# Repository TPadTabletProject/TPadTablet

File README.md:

TPadTablet
==========

Projects developed for TPad Haptic Surface 
by Northwestern NxR Lab

<b>Applications:</b>
  * **IOIOAccessibilityService**: Haptic feedback as an android accessibility service
  * **HelloTPadTablet**: Demo app using on/off, time-based, and space based haptic textures
  * **TPadDepthMap**: Converts image into depth-based haptic feedback system
  * **TPadFrictionMap**: Uses pixels to create friction values for haptic surface
  * **TPadNexusLib**: Contains libraries used for other apps
  * **TimeTextureSampler**: App that allows you change amplitude and frequency of different wave forms for sampling haptic feedback.

Dev Notes:
	TexturePicApp should be fully merged with master branch at this point.

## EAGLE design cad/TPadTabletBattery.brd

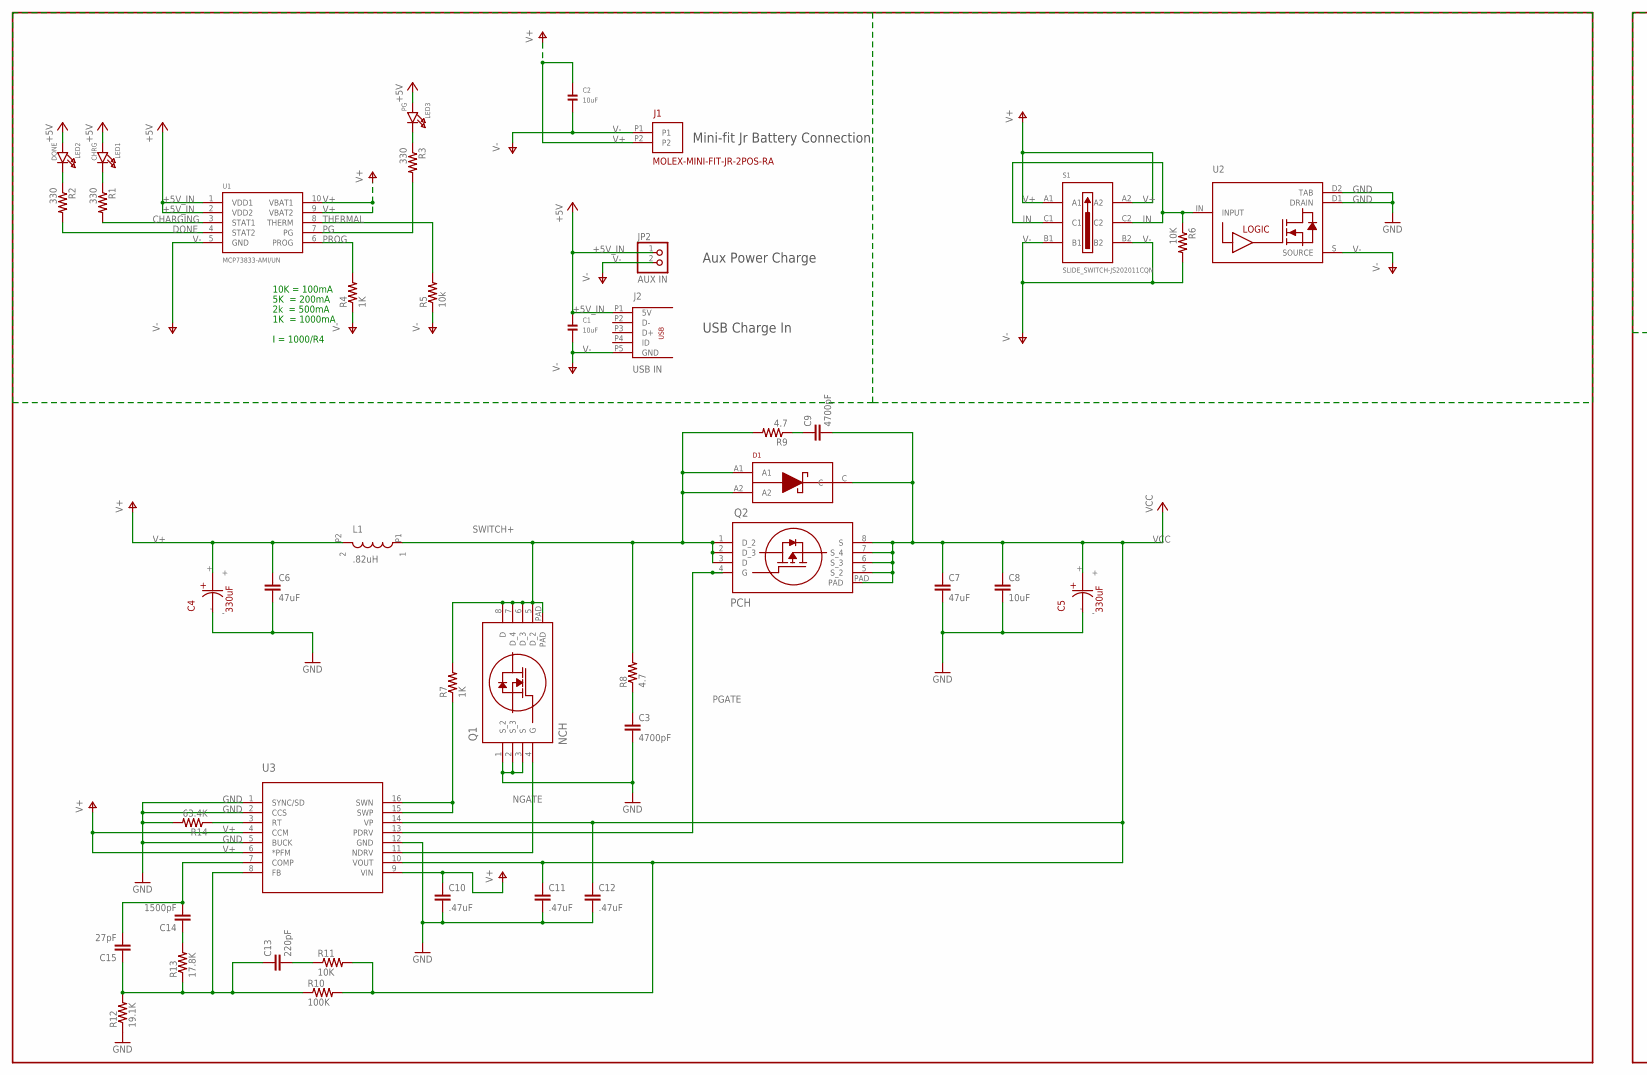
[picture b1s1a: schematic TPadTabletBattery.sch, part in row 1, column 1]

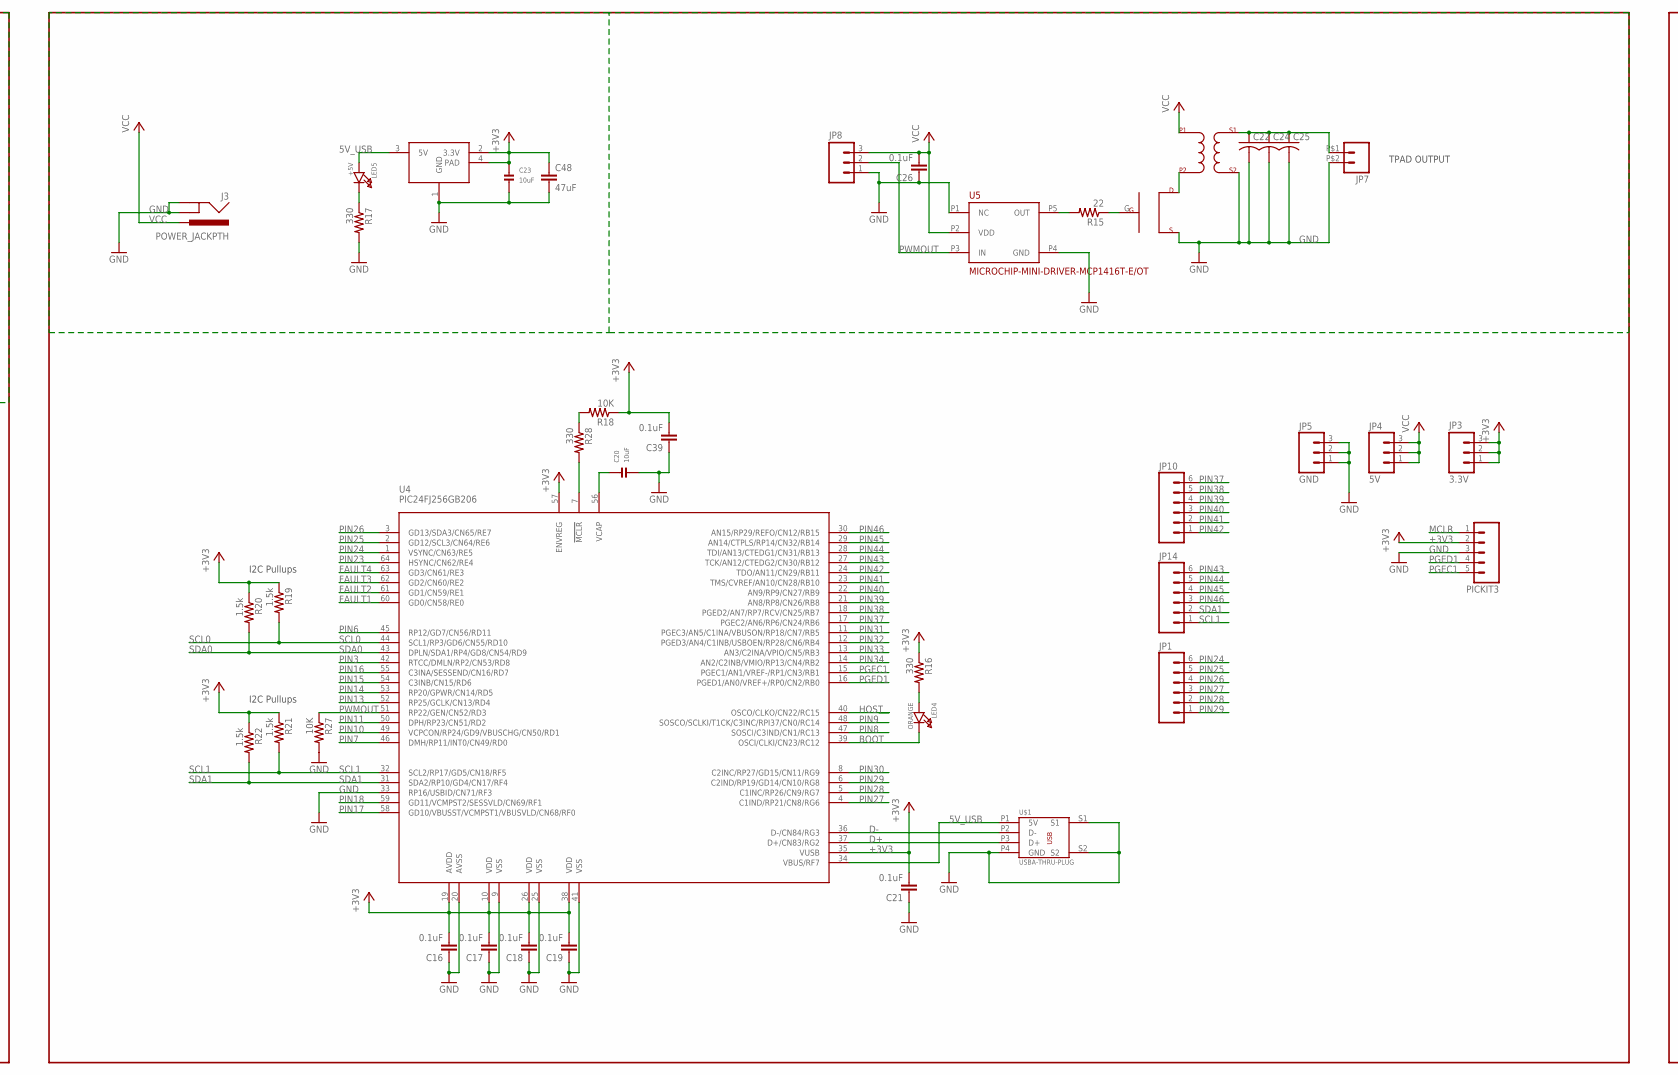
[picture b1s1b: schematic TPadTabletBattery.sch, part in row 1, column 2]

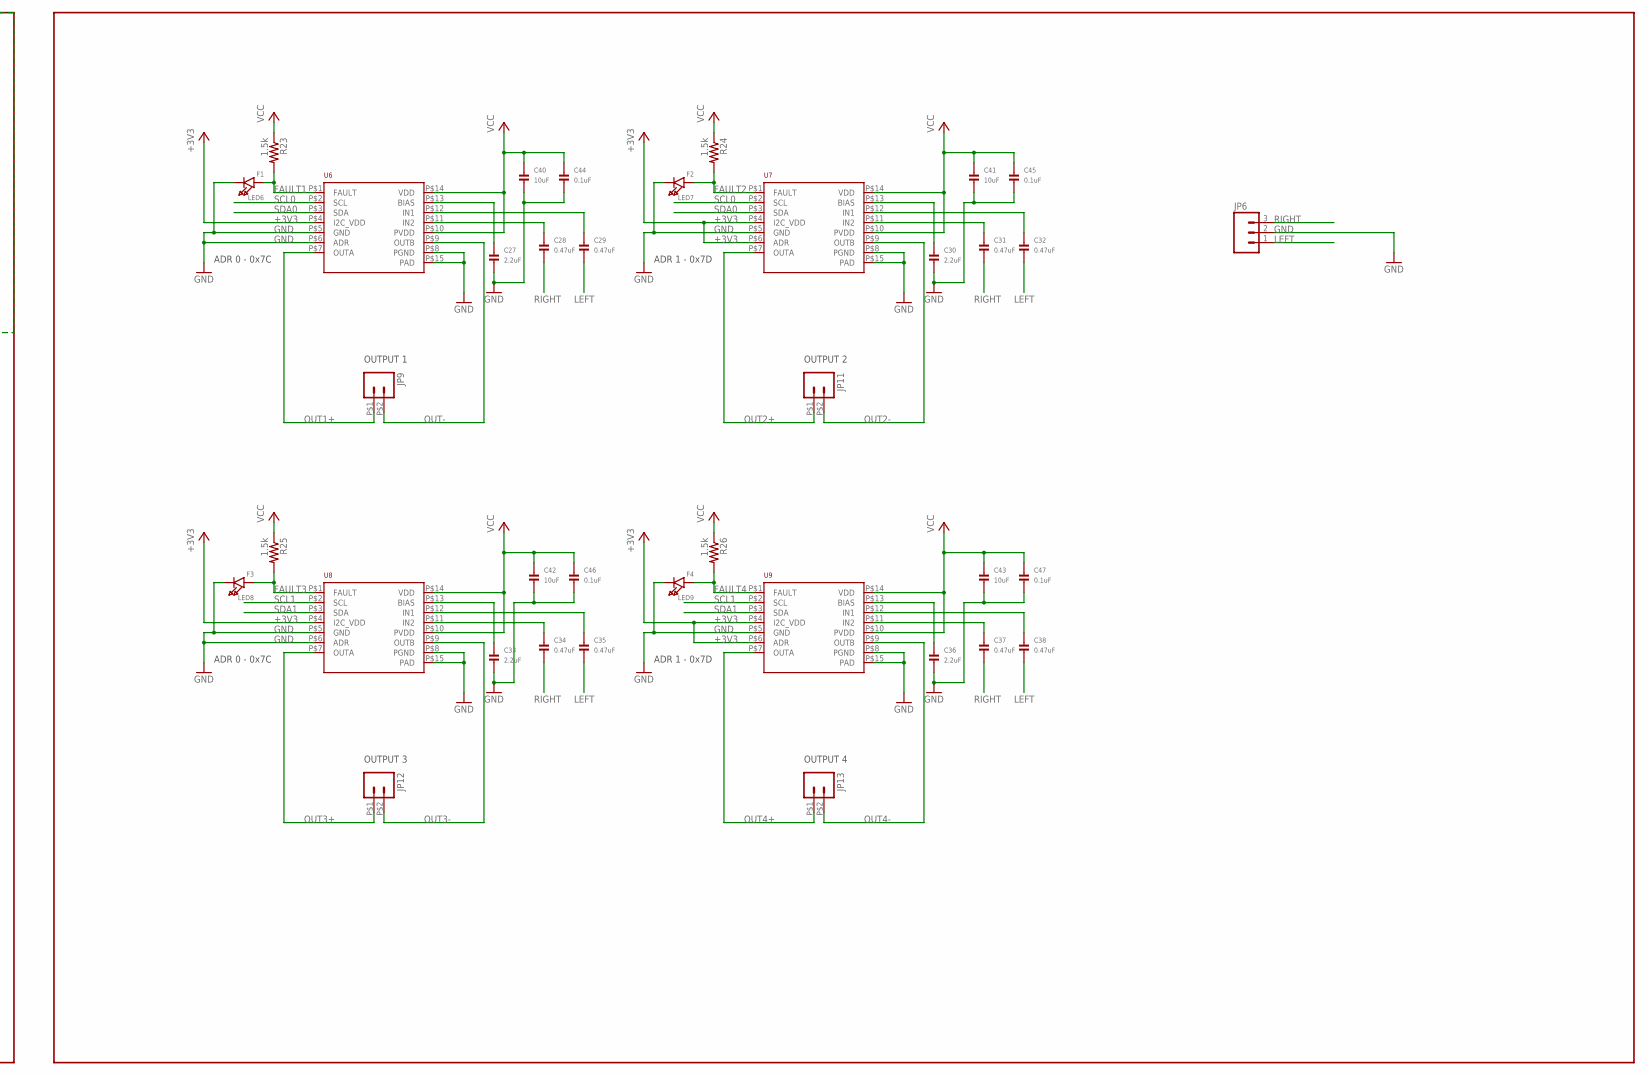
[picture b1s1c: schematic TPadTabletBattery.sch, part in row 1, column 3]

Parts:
C1, C2, C20, C23, C40, C41, C42, C43: 10uF; MICROBUILDER_0805
C3, C9: 4700pF; 0603-CAP
C4, C5: 330uF; 330UF_POSCAP
C6, C7, C48: 47uF; 1210
C8: 10uF; 0805
C10, C11, C12: .47uF; 0603-CAP
C13: 220pF; 0603-CAP
C14: 1500pF; 0603-CAP
C15: 27pF; 0603-CAP
C16, C17, C18, C19, C21, C26, C39: 0.1uF; 0603-CAP
C22, C24, C25: C-US050-035X075; C050-035X075
C27, C30, C33, C36: 2.2uF; MICROBUILDER_0603
C28, C29, C31, C32, C34, C35, C37, C38: 0.47uF; MICROBUILDER_0603
C44, C45, C46, C47: 0.1uF; MICROBUILDER_0603
D1: POWER-DIODE_PDS835L
J1: MOLEX-MINI-FIT-JR-2POS-RA
J2: USB IN; USBMICROBSMT
J3: POWER_JACKPTH; POWER_JACK_PTH
JP1, JP10, JP14: M06SIP; 1X06
JP2: AUX IN; MICROBUILDER_1X02_ROUND
JP3: 3.3V; 1X03
JP4: 5V; 1X03
JP5: GND; 1X03
JP6, JP8: M03PTH; 1X03
JP7, JP9, JP11, JP12, JP13: M02PTH2; 1X02_BIG
L1: .82uH; .82UH_INDUCTOR-IHLP3232DZERR82M01
LED1: CHRG; MICROBUILDER_CHIPLED_0603
LED2: DONE; MICROBUILDER_CHIPLED_0603
LED3: PG; MICROBUILDER_CHIPLED_0603
LED4: ORANGE; MICROBUILDER_CHIPLED_0603
LED5: +5V; MICROBUILDER_CHIPLED_0603
LED6: F1; MICROBUILDER_CHIPLED_0603
LED7: F2; MICROBUILDER_CHIPLED_0603
LED8: F3; MICROBUILDER_CHIPLED_0603
LED9: F4; MICROBUILDER_CHIPLED_0603
PICKIT3: M05PTH; 1X05
Q1: NCH; DQG8
Q2: PCH; DQG8
R1, R2, R3, R16, R17, R28: 330; 0603-RES
R4: 1K; 0805
R5: 10k; 0805
R6, R11, R18, R27: 10K; 0603-RES
R7: 1K; 0603-RES
R8, R9: 4.7; 0603-RES
R10: 100K; 0603-RES
R12: 19.1K; 0603-RES
R13: 17.8K; 0603-RES
R14: 63.4K; 0603-RES
R15: 22; 0603-RES
R19, R20, R21, R22, R23, R24, R25, R26: 1.5k; 0603-RES
S1: SLIDE_SWITCH-JS202011CQN
U1: MCP73833-AMI/UN; MICROBUILDER_MSOP10
U2: STM-LOW-SWITCH-VNL5050N3TR-E; SOT223
U3: TPS43000_PW_16; PW16
U4: PIC24FJ256GB206; PIC24FXXX_TQFP64
U5: MICROCHIP-MINI-DRIVER-MCP1416T-E/OT
U6, U7, U8, U9: TI-AUDIOAMP-LM48100Q
U$1: USBA-THRU-PLUG; USBA-THRU-FLUG
U$4: TRANSFORMER
U$5: TPAD_IRF520N; TPAD_TO220
U$6: LD33V; SOT223

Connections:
5V_USB: LED5.A, U4.34 (VBUS/RF7), U$1.P1 (5V), U$6.3 (5V)
+3V3: C16.2, C17.2, C18.2, C19.2, C21.2, C23.1, C39.2, C48.1, JP3.1, JP3.2, JP3.3, PICKIT3.2, R16.1, R18.1, R19.1, R20.1, R21.1, R22.1, U4.10 (VDD), U4.19 (AVDD), U4.26 (VDD), U4.35 (VUSB), U4.38 (VDD), U4.57 (ENVREG), U6.P$4 (I2C_VDD), U7.P$4 (I2C_VDD), U7.P$6 (ADR), U8.P$4 (I2C_VDD), U9.P$4 (I2C_VDD), U9.P$6 (ADR), U$6.2 (3.3V), U$6.4 (PAD)
+5V_IN: C1.1, J2.P1 (5V), JP2.1, LED1.A, LED2.A, LED3.A, U1.1 (VDD1), U1.2 (VDD2)
BOOT: LED4.C, U4.39 (OSCI/CLKI/CN23/RC12)
CHARGING: R1.2, U1.3 (STAT1)
D+: U4.37 (D+/CN83/RG2), U$1.P3 (D+)
D-: U4.36 (D-/CN84/RG3), U$1.P2 (D-)
DONE: R2.2, U1.4 (STAT2)
FAULT1: LED6.A, R23.2, U4.60 (GD0/CN58/RE0), U6.P$1 (FAULT)
FAULT2: LED7.A, R24.2, U4.61 (GD1/CN59/RE1), U7.P$1 (FAULT)
FAULT3: LED8.A, R25.2, U4.62 (GD2/CN60/RE2), U8.P$1 (FAULT)
FAULT4: LED9.A, R26.2, U4.63 (GD3/CN61/RE3), U9.P$1 (FAULT)
GND: C3.2, C4.-, C5.-, C6.2, C7.2, C8.2, C10.2, C11.2, C12.2, C16.1, C17.1, C18.1, C19.1, C20.2, C21.1, C22.2, C23.2, C24.2, C25.2, C26.1, C27.2, C30.2, C33.2, C36.2, C39.1, C40.2, C41.2, C42.2, C43.2, C44.2, C45.2, C46.2, C47.2, C48.2, J3.GND, J3.GNDBREAK, JP5.1, JP5.2, JP5.3, JP6.2, JP7.P$2 (2), JP8.1, LED6.C, LED7.C, LED8.C, LED9.C, PICKIT3.3, Q1.1 (S_2), Q1.2 (S_3), Q1.3 (S), R12.1, R14.2, R17.2, R27.2, U2.D1 (DRAIN), U2.D2 (TAB), U3.1 (SYNC/SD), U3.2 (CCS), U3.5 (BUCK), U3.12 (GND), U4.9 (VSS), U4.20 (AVSS), U4.25 (VSS), U4.33 (RP16/USBID/CN71/RF3), U4.41 (VSS), U5.P1 (NC), U5.P4 (GND), U6.P$5 (GND), U6.P$6 (ADR), U6.P$8 (PGND), U6.P$15 (PAD), U7.P$5 (GND), U7.P$8 (PGND), U7.P$15 (PAD), U8.P$5 (GND), U8.P$6 (ADR), U8.P$8 (PGND), U8.P$15 (PAD), U9.P$5 (GND), U9.P$8 (PGND), U9.P$15 (PAD), U$1.P4 (GND), U$1.S1, U$1.S2, U$4.S2, U$5.S, U$6.1 (GND)
HOST: U4.40 (OSCO/CLKO/CN22/RC15)
IN: R6.1, S1.C1, S1.C2, U2.IN (INPUT)
LEFT: C29.2, C32.2, C35.2, C38.2, JP6.1
MCLR: PICKIT3.1, R18.2, R28.1
unnamed: R7.1, U3.15 (SWP), U3.16 (SWN)
unnamed: LED2.C, R2.1
unnamed: LED1.C, R1.1
unnamed: LED3.C, R3.1
unnamed: R28.2, U4.7 (!MCLR)
unnamed: C9.1, R9.1
unnamed: C13.1, C15.1, R10.1, R12.2, R13.1, U3.8 (FB)
unnamed: C14.2, C15.2, U3.7 (COMP)
unnamed: C3.1, R8.1
unnamed: C20.1, U4.56 (VCAP)
unnamed: R14.1, U3.3 (RT)
unnamed: C14.1, R13.2
unnamed: LED4.A, R16.2
unnamed: C13.2, R11.1
unnamed: U$4.P2, U$5.D
unnamed: R15.2, U5.P5 (OUT)
unnamed: C22.1, C24.1, C25.1, JP7.P$1 (1), U$4.S1
unnamed: LED5.C, R17.1
unnamed: R15.1, U$5.G
unnamed: C27.1, U6.P$13 (BIAS)
unnamed: C29.1, U6.P$12 (IN1)
unnamed: C28.1, U6.P$11 (IN2)
unnamed: C30.1, U7.P$13 (BIAS)
unnamed: C32.1, U7.P$12 (IN1)
unnamed: C31.1, U7.P$11 (IN2)
unnamed: C33.1, U8.P$13 (BIAS)
unnamed: C35.1, U8.P$12 (IN1)
unnamed: C34.1, U8.P$11 (IN2)
unnamed: C36.1, U9.P$13 (BIAS)
unnamed: C38.1, U9.P$12 (IN1)
unnamed: C37.1, U9.P$11 (IN2)
NGATE: Q1.4 (G), U3.11 (NDRV)
OUT1+: JP9.P$1 (1), U6.P$7 (OUTA)
OUT2+: JP11.P$1 (1), U7.P$7 (OUTA)
OUT2-: JP11.P$2 (2), U7.P$9 (OUTB)
OUT3+: JP12.P$1 (1), U8.P$7 (OUTA)
OUT3-: JP12.P$2 (2), U8.P$9 (OUTB)
OUT4+: JP13.P$1 (1), U9.P$7 (OUTA)
OUT4-: JP13.P$2 (2), U9.P$9 (OUTB)
OUT-: JP9.P$2 (2), U6.P$9 (OUTB)
PG: R3.2, U1.7 (PG)
PGATE: Q2.4 (G), U3.13 (PDRV)
PGEC1: PICKIT3.5, U4.15 (PGEC1/AN1/VREF-/RP1/CN3/RB1)
PGED1: PICKIT3.4, U4.16 (PGED1/AN0/VREF+/RP0/CN2/RB0)
PIN3: U4.42 (RTCC/DMLN/RP2/CN53/RD8)
PIN6: U4.45 (RP12/GD7/CN56/RD11)
PIN7: U4.46 (DMH/RP11/INT0/CN49/RD0)
PIN8: U4.47 (SOSCI/C3IND/CN1/RC13)
PIN9: U4.48 (SOSCO/SCLKI/T1CK/C3INC/RPI37/CN0/RC14)
PIN10: U4.49 (VCPCON/RP24/GD9/VBUSCHG/CN50/RD1)
PIN11: U4.50 (DPH/RP23/CN51/RD2)
PIN13: U4.52 (RP25/GCLK/CN13/RD4)
PIN14: U4.53 (RP20/GPWR/CN14/RD5)
PIN15: U4.54 (C3INB/CN15/RD6)
PIN16: U4.55 (C3INA/SESSEND/CN16/RD7)
PIN17: U4.58 (GD10/VBUSST/VCMPST1/VBUSVLD/CN68/RF0)
PIN18: U4.59 (GD11/VCMPST2/SESSVLD/CN69/RF1)
PIN23: U4.64 (HSYNC/CN62/RE4)
PIN24: JP1.6, U4.1 (VSYNC/CN63/RE5)
PIN25: JP1.5, U4.2 (GD12/SCL3/CN64/RE6)
PIN26: JP1.4, U4.3 (GD13/SDA3/CN65/RE7)
PIN27: JP1.3, U4.4 (C1IND/RP21/CN8/RG6)
PIN28: JP1.2, U4.5 (C1INC/RP26/CN9/RG7)
PIN29: JP1.1, U4.6 (C2IND/RP19/GD14/CN10/RG8)
PIN30: U4.8 (C2INC/RP27/GD15/CN11/RG9)
PIN31: U4.11 (PGEC3/AN5/C1INA/VBUSON/RP18/CN7/RB5)
PIN32: U4.12 (PGED3/AN4/C1INB/USBOEN/RP28/CN6/RB4)
PIN33: U4.13 (AN3/C2INA/VPIO/CN5/RB3)
PIN34: U4.14 (AN2/C2INB/VMIO/RP13/CN4/RB2)
PIN37: JP10.6, U4.17 (PGEC2/AN6/RP6/CN24/RB6)
PIN38: JP10.5, U4.18 (PGED2/AN7/RP7/RCV/CN25/RB7)
PIN39: JP10.4, U4.21 (AN8/RP8/CN26/RB8)
PIN40: JP10.3, U4.22 (AN9/RP9/CN27/RB9)
PIN41: JP10.2, U4.23 (TMS/CVREF/AN10/CN28/RB10)
PIN42: JP10.1, U4.24 (TDO/AN11/CN29/RB11)
PIN43: JP14.6, U4.27 (TCK/AN12/CTEDG2/CN30/RB12)
PIN44: JP14.5, U4.28 (TDI/AN13/CTEDG1/CN31/RB13)
PIN45: JP14.4, U4.29 (AN14/CTPLS/RP14/CN32/RB14)
PIN46: JP14.3, U4.30 (AN15/RP29/REFO/CN12/RB15)
PROG: R4.2, U1.6 (PROG)
PWMOUT: JP8.2, R27.1, U4.51 (RP22/GEN/CN52/RD3), U5.P3 (IN)
RIGHT: C28.2, C31.2, C34.2, C37.2, JP6.3
SCL0: R19.2, U4.44 (SCL1/RP3/GD6/CN55/RD10), U6.P$2 (SCL), U7.P$2 (SCL)
SCL1: JP14.1, R21.2, U4.32 (SCL2/RP17/GD5/CN18/RF5), U8.P$2 (SCL), U9.P$2 (SCL)
SDA0: R20.2, U4.43 (DPLN/SDA1/RP4/GD8/CN54/RD9), U6.P$3 (SDA), U7.P$3 (SDA)
SDA1: JP14.2, R22.2, U4.31 (SDA2/RP10/GD4/CN17/RF4), U8.P$3 (SDA), U9.P$3 (SDA)
SWITCH+: D1.A1, D1.A2, L1.P1 (1), Q1.5 (D_2), Q1.6 (D_3), Q1.7 (D_4), Q1.8 (D), Q1.PAD, Q2.1 (D_2), Q2.2 (D_3), Q2.3 (D), R7.2, R8.2, R9.2
THERMAL: R5.2, U1.8 (THERM)
V+: C2.1, C4.+, C6.1, C10.1, J1.P2, L1.P2 (2), S1.A1, S1.A2, U1.9 (VBAT2), U1.10 (VBAT1), U3.4 (CCM), U3.6 (*PFM), U3.9 (VIN)
V-: C1.2, C2.2, J1.P1, J2.P5 (GND), JP2.2, R4.1, R5.1, R6.2, S1.B1, S1.B2, U1.5 (GND), U2.S (SOURCE)
VCC: C5.+, C7.1, C8.1, C9.2, C11.1, C12.1, C26.2, C40.1, C41.1, C42.1, C43.1, C44.1, C45.1, C46.1, C47.1, D1.C, J3.PWR, JP4.1, JP4.2, JP4.3, JP8.3, Q2.5 (S_2), Q2.6 (S_3), Q2.7 (S_4), Q2.8 (S), Q2.PAD, R10.2, R11.2, R23.1, R24.1, R25.1, R26.1, U3.10 (VOUT), U3.14 (VP), U5.P2 (VDD), U6.P$10 (PVDD), U6.P$14 (VDD), U7.P$10 (PVDD), U7.P$14 (VDD), U8.P$10 (PVDD), U8.P$14 (VDD), U9.P$10 (PVDD), U9.P$14 (VDD), U$4.P1

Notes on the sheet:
10K = 100mA
5K = 200mA
2k = 500mA
1K = 1000mA
I = 1000/R4
Mini-fit Jr Battery Connection
USB Charge In
Aux Power Charge
ADR 0 - 0x7C
I2C Pullups
OUTPUT 1
TPAD OUTPUT
OUTPUT 2
ADR 1 - 0x7D
OUTPUT 3
OUTPUT 4

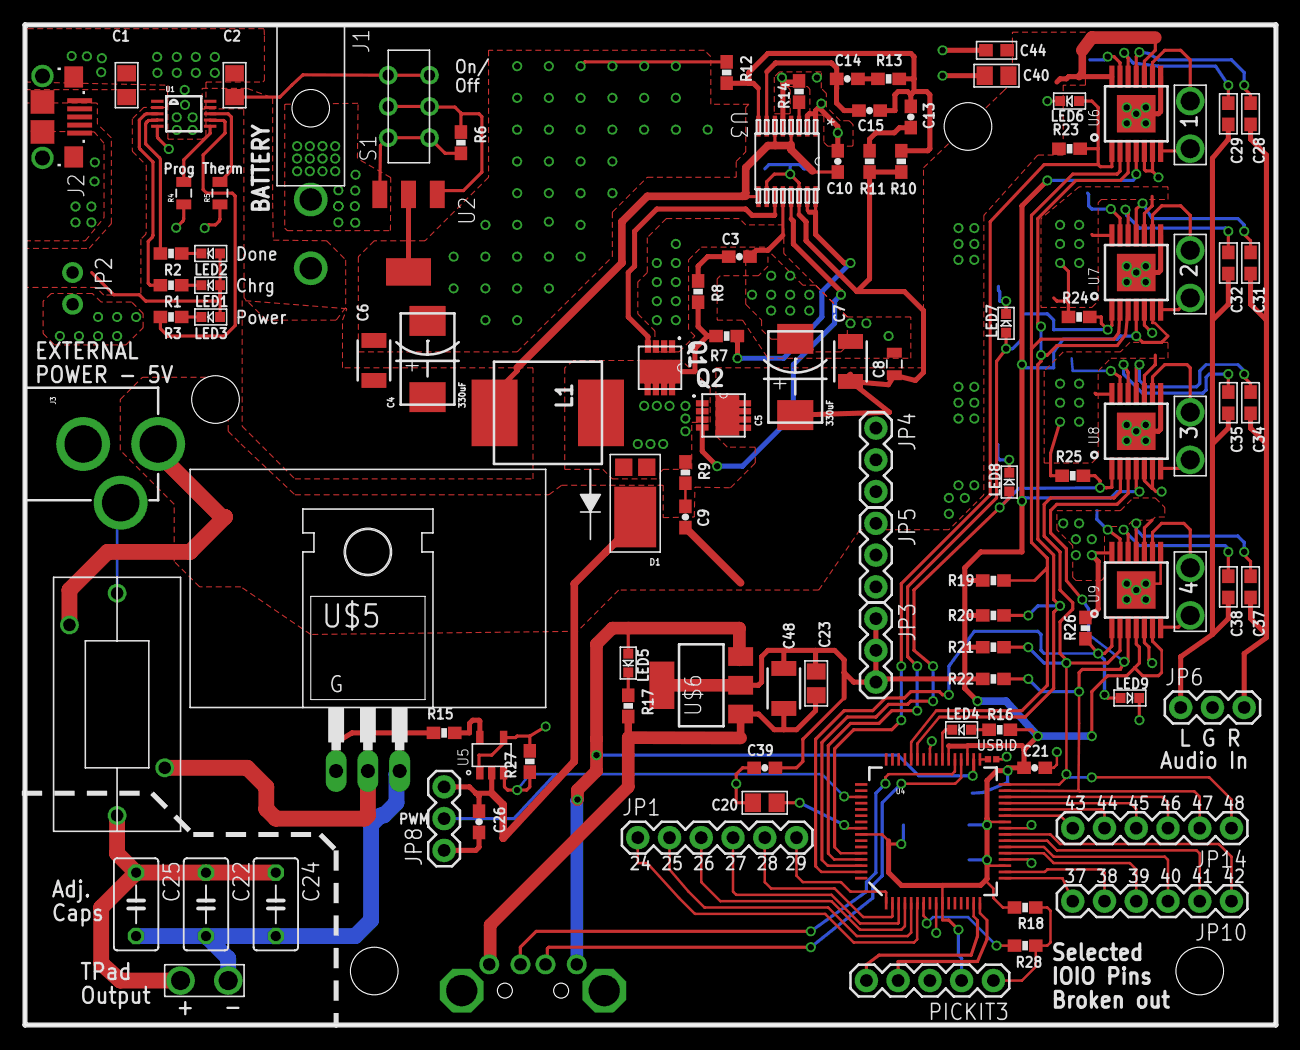
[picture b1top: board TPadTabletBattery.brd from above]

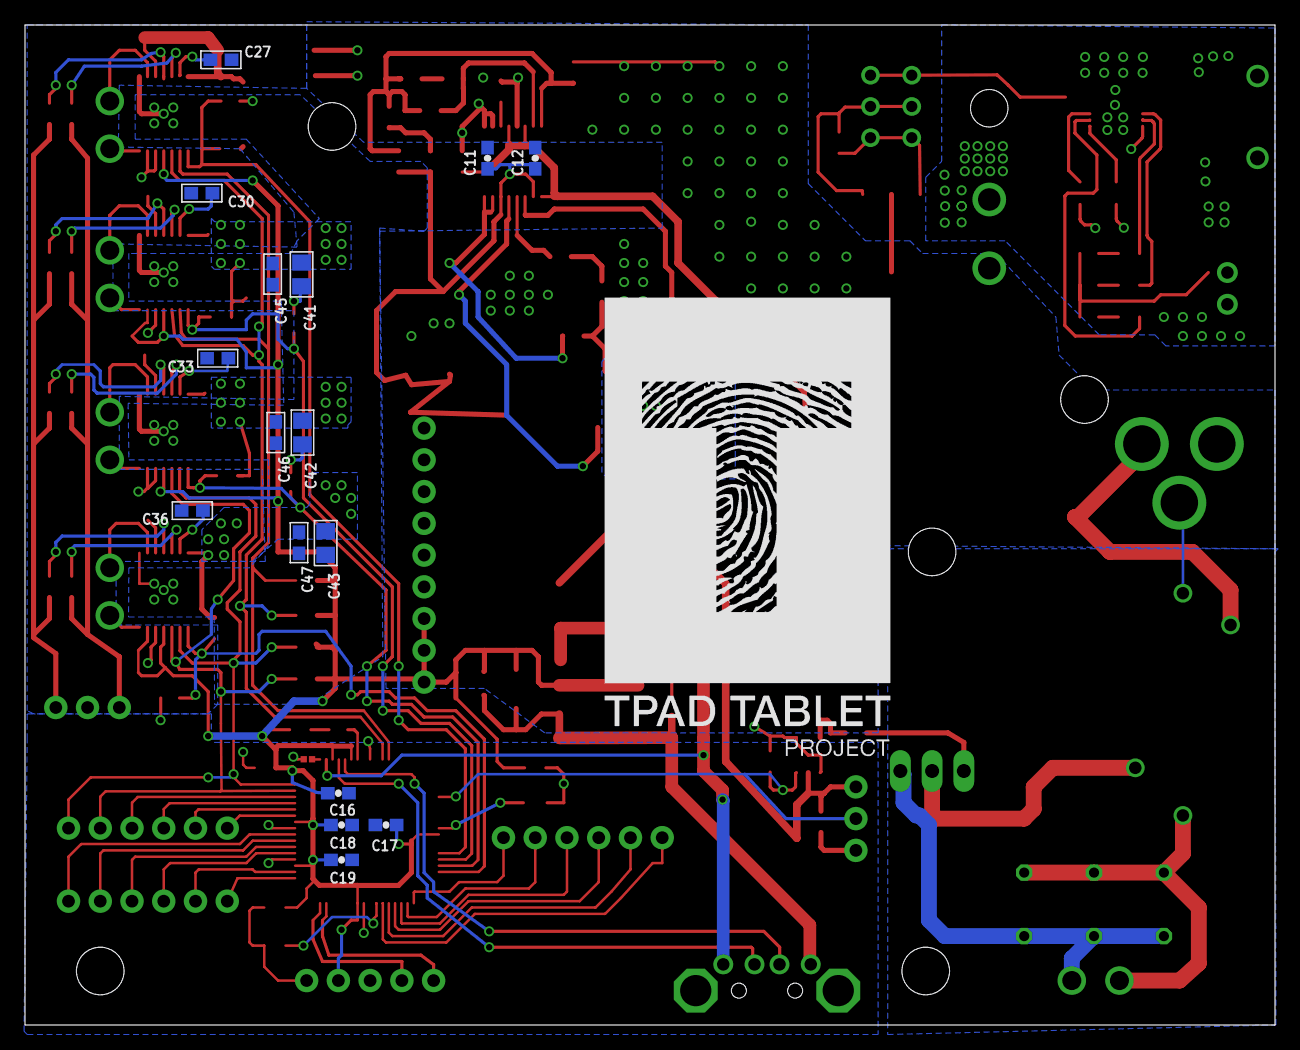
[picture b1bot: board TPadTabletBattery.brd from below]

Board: 2 copper layers, 100.0 x 80.0 mm, 122 parts (17 on the bottom side), 88 nets.

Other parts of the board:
U$2: TPADTABLETPROJECT

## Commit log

2014-06-16 Initial Library Commit
    This includes the TPadIOIO library to be used with the Nexus 7 TPads.
    Also included is a HelloWorld TPad Example application
2014-06-16 Fixing TPadIOIOLib support jar issue
2014-06-16 Update June 16th
2014-06-16 Uploading Demo Apps
    Upload Workshop and Gradient Demos
2014-06-17 Renaming Apps and Libraires
2014-06-18 Changes to HelloTPadTablet
    Also include some changes and additions to TPadNexusLib
2014-06-20 updating readme
2014-06-20 added incomplete project listing
2014-06-20 quick fix
2014-06-23 Including pre-compiled IOIO .jar files
    The TPadNexus Library now has the IOIO libraries included with it in the
    libs folder
2014-06-25 Fixed OpenCV Loading error
    The app will now ask for you to install the opencv manager if it is
    not
    already installed on the tablet.
2014-06-25 Changed Paths to Relative
    Changed TPadNexusLibrary to include relative path .jar files
2014-06-30 Added support for binding to background service to get Frequency
2014-07-01 ioio accessibility service
2014-07-01 Updates to HelloTPadTablet
2014-07-01 Revert "Updates to HelloTPadTablet"
    This reverts commit 2b77ea952065f636da8204cc40c6355d013fe76b.
2014-07-01 undo previous push to keep HelloTPadTablet working
2014-07-02 Updating main-service branch with my local repo
2014-07-02 removing .class files
2014-07-02 Updating the manifest to stop it from asking for USB access
2014-07-02 changing to flags for textures
2014-07-02 clearing cache
2014-07-03 removal of carriage return
2014-07-03 added gitignore
2014-07-03 git cache cleared
2014-07-07 TimeTextureApp
2014-07-07 Connected to the testing area view
2014-07-07 got graph to show up
2014-07-08 Added the Grapher functionality
2014-07-08 added gitignore to master
2014-07-08 cache cleared
2014-07-09 Removed scale factor in FrictionMap so that properly sized pictures would appear properly on the phone
2014-07-10 set the seek bars properly due to log difference
2014-07-10 textView1 remvoed and button no longer affects anything
2014-07-10 removed the button, fixed positioning of the checkbox
2014-07-10 moved spinners around to make UI clearer
2014-07-10 side by side spinners
2014-07-10 updates to sawtooth function to correct frequency error
2014-07-10 tweaking properties
2014-07-10 added Home, Back, and Recent Apps textures
2014-07-10 Seekbar min changed to .25 and UI element adjusted accordingly
2014-07-10 Changed the frequency to that of my TPad
2014-07-10 solving some issues with Recent apps button, ended up being a capitalization error
2014-07-21 Removed some of the toasts
2014-08-15 Adding dynamichaptic file
2014-08-19 changes to nexusactivity for service
2014-08-20 dependencies adjustments
2014-08-21 minor prop changes
2014-08-21 Bringing in MainScreen with graphing function from TexturePicApp branch to master branch, in prep for merge
2014-08-21 Added commets for readability
2014-08-22 Updated the properties
2014-09-11 updating to fix a few crash bugs
2014-10-15 modified: software/TPadNexusLib/project.properties software/Comet/ software/HapticsMessage/
2014-10-15 Uploading of CHI 14 Study Applications
2014-10-17 Adding TPad Haptic Canvas, used in CHI study
2014-10-21 Uploading BOM and Eagle CAD Files
2014-10-22 USB OTG board version updated
2014-10-22 Updated BOM and Zip File

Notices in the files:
parts and their libraries:
SparkFun-Passives: Licensing: CC v3.0 Share-Alike You are welcome to use this library for commercial purposes.
